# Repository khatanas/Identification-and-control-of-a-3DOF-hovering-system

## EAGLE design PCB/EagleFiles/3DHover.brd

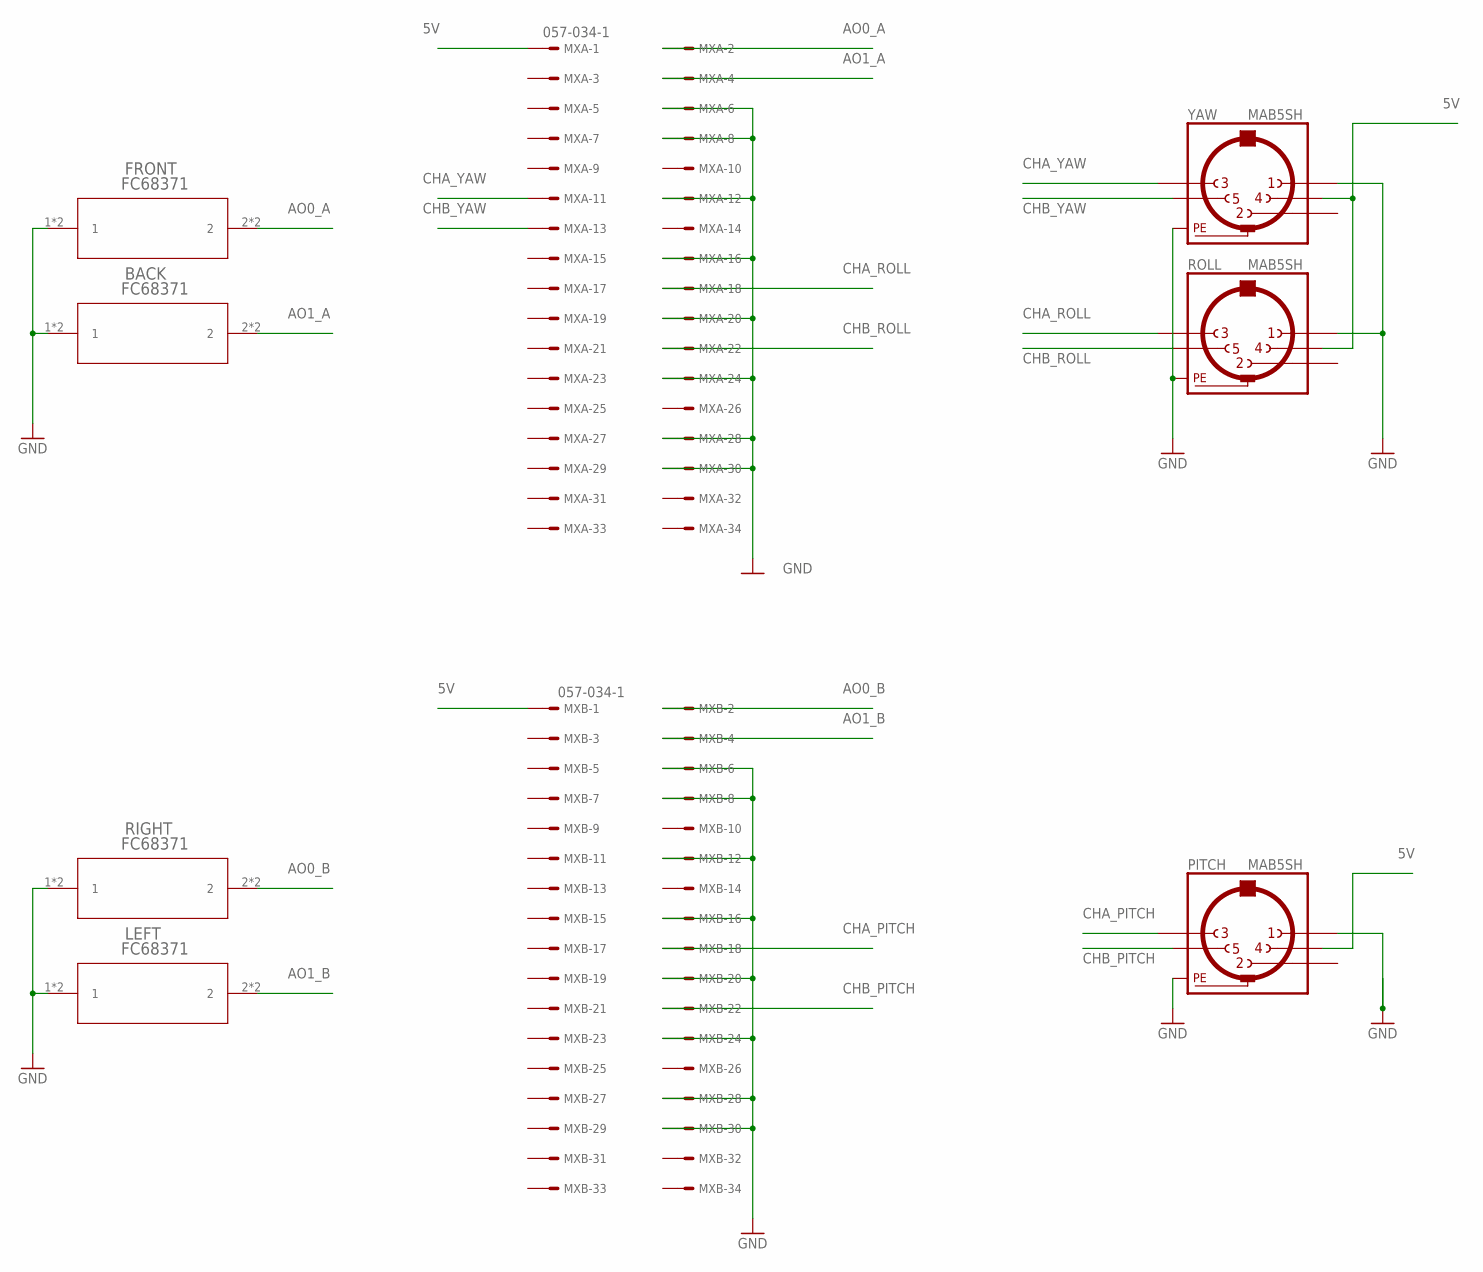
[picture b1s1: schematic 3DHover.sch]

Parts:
BACK: FC68371; FC68371_CLF
FRONT: FC68371; FC68371_CLF
LEFT: FC68371; FC68371_CLF
MXA: 057-034-1
MXB: 057-034-1
PITCH: MAB5SH
RIGHT: FC68371; FC68371_CLF
ROLL: MAB5SH
YAW: MAB5SH

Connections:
5V: MXA.1, MXB.1, PITCH.4, ROLL.4, YAW.4
AO0_A: FRONT.2, FRONT.4 (2), MXA.2
AO0_B: MXB.2, RIGHT.2, RIGHT.4 (2)
AO1_A: BACK.2, BACK.4 (2), MXA.4
AO1_B: LEFT.2, LEFT.4 (2), MXB.4
CHA_PITCH: MXB.18, PITCH.3
CHA_ROLL: MXA.18, ROLL.3
CHA_YAW: MXA.11, YAW.3
CHB_PITCH: MXB.22, PITCH.5
CHB_ROLL: MXA.22, ROLL.5
CHB_YAW: MXA.13, YAW.5
GND: BACK.1, BACK.3 (1), FRONT.1, FRONT.3 (1), LEFT.1, LEFT.3 (1), MXA.6, MXA.8, MXA.12, MXA.16, MXA.20, MXA.24, MXA.28, MXA.30, MXB.6, MXB.8, MXB.12, MXB.16, MXB.20, MXB.24, MXB.28, MXB.30, PITCH.1, PITCH.PE, PITCH.PE@ (PE), RIGHT.1, RIGHT.3 (1), ROLL.1, ROLL.PE, ROLL.PE@ (PE), YAW.1, YAW.PE, YAW.PE@ (PE)

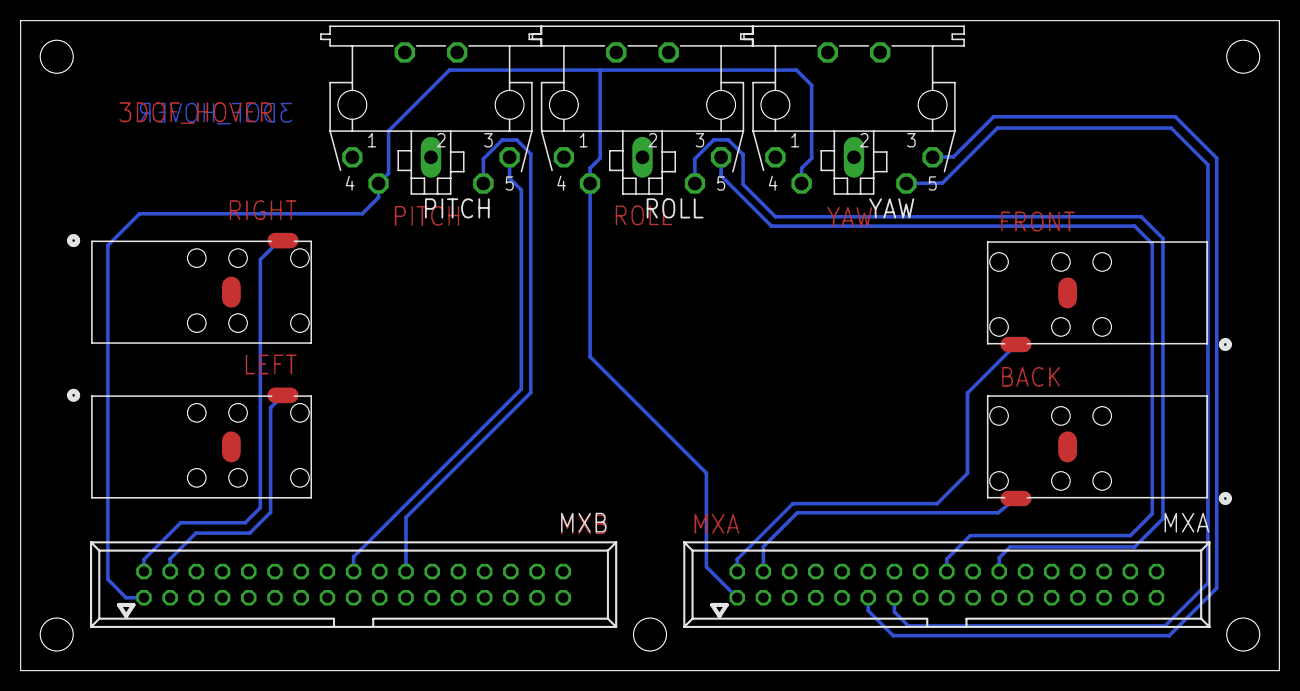
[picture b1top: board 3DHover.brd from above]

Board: 2 copper layers, 122.0 x 63.0 mm, 9 parts (0 on the bottom side), 12 nets.

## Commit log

2023-01-09 adding files
2023-01-09 removed fcts
2023-01-10 qp ok
2023-01-10 qp done, MIMO id ok
2023-01-11 solved yaw qp issue and performed MIMO sysID
2023-01-11 qp done with graphs
2023-01-12 final
2023-01-16 adding dd controller
2023-06-10 Rename README.txt.txt to README.md

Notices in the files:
parts and their libraries:
COPYRIGHT: Copyright (C) 2022 Ultra Librarian. All rights reserved.
